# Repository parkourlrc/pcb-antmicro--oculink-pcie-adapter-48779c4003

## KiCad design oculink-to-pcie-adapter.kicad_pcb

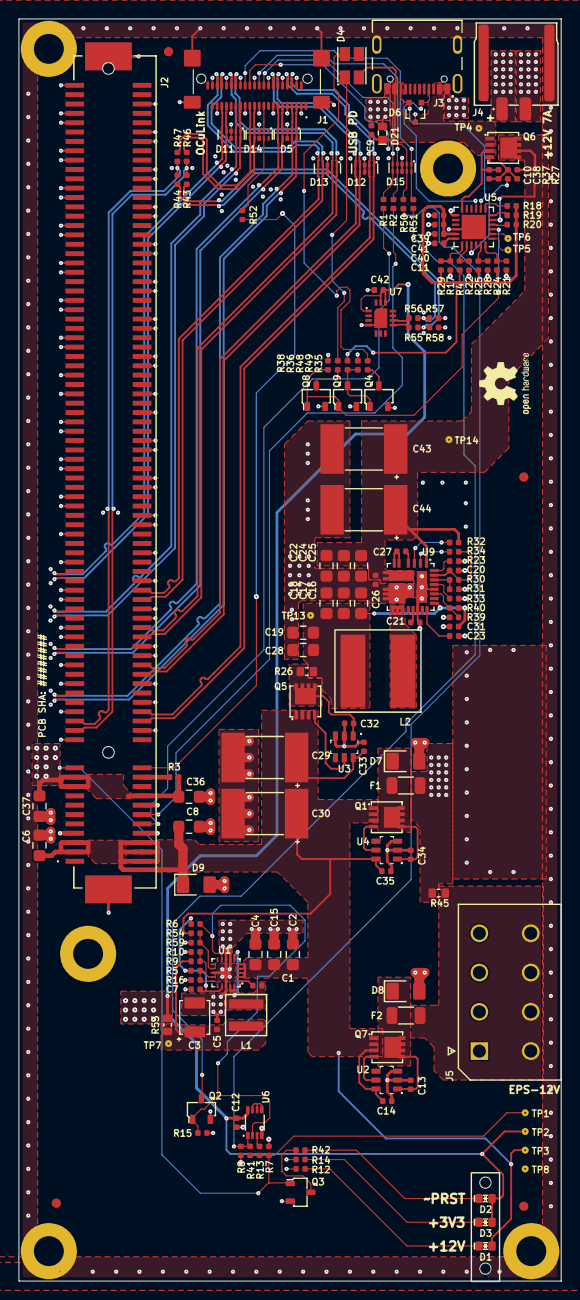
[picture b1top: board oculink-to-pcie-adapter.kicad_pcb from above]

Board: 4 copper layers, 58.0 x 135.0 mm, 159 parts (0 on the bottom side), 97 nets.

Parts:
C1, C12, C13, C26, C27, C31, C32, C34, C40, C41, C42: C_100n_0402; C_0402_1005Metric
C2, C4, C15, C16, C17, C18, C19, C28: C_22u_25V_0805; C_0805_2012Metric
C3: C_Pol_100u_10V_KEMET-T520-B; C_Pol_EIA-B
C5, C7, C10, C11, C14, C20, C33, C35, C38, C39: C_1u_25V_0402; C_0402_1005Metric
C6, C8, C22, C24, C25, C36, C37: C_10u_0805_35V; C_0805_2012Metric
C9, C21: C_4u7_25V_0402; C_0402_1005Metric
C23: C_33n_0402; C_0402_1005Metric
C29, C30, C43, C44: C_Pol_150u_30V_Vishay-T59-EE; C_Pol_Vishay-T59-EE
D1, D2, D3: LED_G_0603_LTST-C190GKT; LED_0603_1608Metric_G
D4: LED_RGB_PLCC4_ASMB_MTB1_0A3A2; PLCC4_3.2x2.8mm
D5, D11, D12, D13, D14, D15: ESD204DQAR; USON-10_2.5x1mm_P0.5mm
D6: TPD2E2U06_SC70; SC70-3
D7, D8, D9: SZSMF4L14AT3G; SOD-123FL
D21: ESDA25P35-1U1M; QFN-2L_1.6x1x0.55mm
F1, F2: F_7A_1206; F_1206_3216Metric
H1: Lightpipe_Mentor_1296.2013; Mech_Lightpipe_Mentor_1296.2013
J1: OCuLink_x4_Amphenol_G14A421211112HR_CUSTOM_device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; Amphenol_G14A421211112HR
J2: PCIe_x16_10146070-113Y0LF-vertical; AMPHENOL_10146070-113Y0LF
J3: USB-C_GCT_USB4105-GF-A; USB-C_Receptacle_GCT_USB4105-GF-A
J4: Molex_Nano-Fit_1x2_SMD_1054301202; Conn_Molex_Nano-Fit_1x2_SMD_1054301202
J5: Molex_Mini-Fit-Jr_2x4_39-28-8080; MOLEX_39288080
L1: L_1u8_6.8A_WE-MAPI-4020; L_WE-MAPI-4020
L2: L_4u7_14.6A_Abracon-Q8080; L_Abracon_ASPIAIG-Q8080
MP1, MP2, MP3, MP4, MP5: MP_Pad6mm_Drill3.2mm
Q1, Q5, Q6, Q7: SQS401EN-T1_BE3; Vishay_PowerPAK_1212-8_Single
Q2, Q3, Q4, Q8, Q9: BSS138-7-F; SOT-23-3
R1, R2, R3, R13, R30, R41, R43, R44, R46, R47, R50, R51, R52: R_0R_0402; R_0402_1005Metric
R4, R14, R17, R21, R22, R24, R25, R28, R29, R37, R42, R48: R_1k_0402; R_0402_1005Metric
R5, R9, R31, R35: R_68k_0402; R_0402_1005Metric
R6, R12, R16, R27, R36, R38, R49, R54: R_10k_0402; R_0402_1005Metric
R7, R8, R15, R32, R34: R_100k_0402; R_0402_1005Metric
R10: R_15k_0402; R_0402_1005Metric
R18, R19, R23: R_2k_0402; R_0402_1005Metric
R20: R_49k9_0402; R_0402_1005Metric
R26, R45, R53: R_0R_22.4A_0603; R_0603_1608Metric
R33: R_158k_0402; R_0402_1005Metric
R39: R_10k_0.1%_0402; R_0402_1005Metric
R40: R_140k_0.1%_0402; R_0402_1005Metric
R55, R56: R_22R_0402; R_0402_1005Metric
R57, R58: R_50R_0402; R_0402_1005Metric
R59: R_1k5_0402; R_0402_1005Metric
TP1, TP2, TP3, TP4, TP5, TP6, TP7, TP8, TP13, TP14: TP_Pad0.75mm_Drill0.2mm
U1: TPS56C230; QFN-20-1EP_3x3mm_P0.45mm
U2, U3, U4: LTC4412IS6; SOT-23-6
U5: CYPD3177-24LQXQ; QFN-24-1EP_4x4mm_P0.5mm_EP2.6x2.6mm
U6: 74AUP2G132; VSSOP-8_2.3x2mm_P0.5mm
U7: DSC557-0343FI1; VQFN-14-1EP_3.2x2.5mm_P0.5mm_Layout4x3
U9: SIC477ED-T1-GE3; SIC47XED-T1-GE3

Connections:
+3V3: C12.2, C36.1, C37.1, C42.2, D2.2 (A), D3.2 (A), J2.A9, J2.A10, J2.B8, R3.1, R53.1, TP2.1, U6.8 (VCC), U7.1 (OE), U7.12 (VDD1), U7.13 (VDD0)
+12V: C2.2, C4.2, C6.1, C8.1, C14.2, C15.2, C29.1, C30.1, C33.2, C35.2, D1.2 (A), D9.1 (C), J2.A2, J2.A3, J2.B1, J2.B2, J2.B3, Q1.1 (S), Q1.2 (S), Q1.3 (S), Q5.1 (S), Q5.2 (S), Q5.3 (S), Q7.1 (S), Q7.2 (S), Q7.3 (S), R54.1, TP3.1, U1.2 (V_{IN}), U1.3 (V_{IN}), U1.4 (V_{IN}), U1.5 (V_{IN}), U2.6 (SENSE), U3.6 (SENSE), U4.6 (SENSE)
/OCuLink/I2C0.SCL: J2.B5, R1.2
/OCuLink/I2C0.SDA: J2.B6, R2.2
/OCuLink/I2C0C_SCL: D15.5, D15.6, J1.A9 (SCL), R1.1
/OCuLink/I2C0C_SDA: D15.4, D15.7, J1.A10 (SDA), R2.1
/OCuLink/PCIe_{REF0}.CK+: J2.A13, R43.2, R46.2
/OCuLink/PCIe_{REF0}.CK-: J2.A14, R44.2, R47.2
/OCuLink/PCIe_{REF0}_R.CK+: D14.4, D14.7, J1.B12 (VSP1), R46.1
/OCuLink/PCIe_{REF0}_R.CK-: D14.5, D14.6, J1.B13 (VSP2), R47.1
/OCuLink/PCIe_{x4}.RX0+: D5.1, D5.10, J1.B3 (PET0+), J2.A16
/OCuLink/PCIe_{x4}.RX0-: D5.2, D5.9, J1.B4 (PET0-), J2.A17
/OCuLink/PCIe_{x4}.RX1+: D5.4, D5.7, J1.B6 (PET1+), J2.A21
/OCuLink/PCIe_{x4}.RX1-: D5.5, D5.6, J1.B7 (PET1-), J2.A22
/OCuLink/PCIe_{x4}.RX2+: D11.1, D11.10, J1.B15 (PET2+), J2.A25
/OCuLink/PCIe_{x4}.RX2-: D11.2, D11.9, J1.B16 (PET2-), J2.A26
/OCuLink/PCIe_{x4}.RX3+: D11.4, D11.7, J1.B18 (PET3+), J2.A29
/OCuLink/PCIe_{x4}.RX3-: D11.5, D11.6, J1.B19 (PET3-), J2.A30
/OCuLink/PCIe_{x4}.TX0+: D12.1, D12.10, J1.A3 (PER0+), J2.B14
/OCuLink/PCIe_{x4}.TX0-: D12.2, D12.9, J1.A4 (PER0-), J2.B15
/OCuLink/PCIe_{x4}.TX1+: D12.4, D12.7, J1.A6 (PER1+), J2.B19
/OCuLink/PCIe_{x4}.TX1-: D12.5, D12.6, J1.A7 (PER1-), J2.B20
/OCuLink/PCIe_{x4}.TX2+: D13.1, D13.10, J1.A15 (PER2+), J2.B23
/OCuLink/PCIe_{x4}.TX2-: D13.2, D13.9, J1.A16 (PER2-), J2.B24
/OCuLink/PCIe_{x4}.TX3+: D13.4, D13.7, J1.A18 (PER3+), J2.B27
/OCuLink/PCIe_{x4}.TX3-: D13.5, D13.6, J1.A19 (PER3-), J2.B28
/OCuLink/~CPRSNTC: D15.1, D15.10, J1.A13 (~CPRSNT), R51.1
/OCuLink/~CPRSNT: Q2.3 (D), R51.2
/OCuLink/~PERSTC: D15.2, D15.9, J1.A12 (~PERST), R50.1
/OCuLink/~WAKEC: D14.2, D14.9, J1.B10 (~CWAKE), R52.1
/OCuLink/~WAKE: J2.B11, R52.2
/PCIe-clock-generator/PCIe_{REF1}_R2.CK+: R55.1, U7.8 (CLK1+)
/PCIe-clock-generator/PCIe_{REF1}_R2.CK-: R56.1, U7.9 (CLK1-)
/PCIe-clock-generator/PCIe_{REF1}_R.CK+: R43.1, R55.2, R58.2
/PCIe-clock-generator/PCIe_{REF1}_R.CK-: R44.1, R56.2, R57.2
/PCIe-connector/3V3_PCIe_AUX: J2.B10, R3.2
/Power/3V3_BST: C1.1, U1.1 (BST)
/Power/3V3_CONV: C3.1, C5.2, L1.2, R9.2, R53.2, TP7.1
/Power/3V3_EN: R54.2, R59.2, U1.12 (EN)
/Power/3V3_FB: R9.1, R10.2, U1.14 (FB)
/Power/3V3_MODE: R5.1, R16.1, U1.15 (MODE)
/Power/3V3_PG: Q2.1 (G), R6.2, R15.2, U1.9 (PG), U6.2 (1B)
/Power/3V3_SW: C1.2, L1.1, U1.6 (SW), U1.19 (SW), U1.20 (SW)
/Power/3V3_VCC: C7.2, R5.2, R6.1, U1.17 (V_{CC})
/Power/Ideal-diode-1/VIN: C34.2, D7.1 (C), F1.2, Q1.5 (D), U4.1 (IN)
/Power/Ideal-diode-2/VIN: C13.2, D8.1 (C), F2.2, Q7.5 (D), U2.1 (IN)
/Power/PERST: U6.5 (2A), U6.6 (2B), U6.7 (1Y)
/Power/VCC_DC_CONN_1: F1.1, J4.1, R45.2
/Power/VCC_DC_CONN_2: F2.1, J5.5, J5.6, J5.7, J5.8, R45.1
/Power/VCC_PD: C32.2, Q5.5 (D), R26.1, U3.1 (IN)
/Power/~PERST_CONN: R8.2, R41.1, R50.2, U6.1 (1A)
/Power/~PERST: J2.A11, Q3.1 (G), R7.2, R13.2, R41.2, TP1.1
/USB-PD/12V_BOOT: C27.1, U9.4 (BOOT)
/USB-PD/12V_CONV: C16.2, C17.2, C18.2, C19.2, C28.2, C31.2, L2.2, R26.2, R40.2, TP13.1, U9.20 (V_{SNS})
/USB-PD/12V_EN: R32.1, U9.3 (EN)
/USB-PD/12V_FB: R39.2, R40.1, U9.22 (V_{FB})
/USB-PD/12V_FSW: R33.2, U9.24 (f_{SW})
/USB-PD/12V_ILIM: R30.2, R31.2, U9.25 (I_{LIMIT})
/USB-PD/12V_MODE: R23.1, U9.27 (MODE)
/USB-PD/12V_PG: R34.1, U9.2 (P_{GOOD})
/USB-PD/12V_SS: C23.1, U9.19 (SS)
/USB-PD/12V_SW: L2.1, U9.12 (SW), U9.13 (SW), U9.14 (SW)
/USB-PD/12V_VDD: C20.2, R30.1, R34.2, U9.26 (V_{DD})
/USB-PD/12V_VDRV: C21.2, U9.16 (V_{DRV})
/USB-PD/CC1: D6.1, J3.A5 (CC_{1}), U5.15 (CC1)
/USB-PD/CC2: D6.2, J3.B5 (CC_{2}), U5.14 (CC2)
/USB-PD/FAULT: Q8.1 (G), Q9.1 (G), R38.2, U5.9 (FAULT)
/USB-PD/FLIP: R20.1, U5.10 (FLIP)
/USB-PD/GPIO_1: TP6.1, U5.8 (GPIO_1)
/USB-PD/ISNK_COARSE: R25.1, R28.2, U5.5 (ISNK_COARSE)
/USB-PD/ISNK_FINE: R21.2, R24.1, U5.6 (ISNK_FINE)
/USB-PD/SCL: R18.1, U5.13 (HPI_SCL)
/USB-PD/SDA: R19.1, U5.12 (HPI_SDA)
/USB-PD/VBUS_EN: R37.1, U5.3 (VBUS_FET_EN)
/USB-PD/VBUS_MAX: R4.1, R22.2, U5.2 (VBUS_MAX)
/USB-PD/VBUS_MIN: R17.2, R29.1, U5.1 (VBUS_MIN)
/USB-PD/VCC: C22.2, C24.2, C25.2, C26.2, C38.2, C43.1, C44.1, Q6.5 (D), R32.2, TP14.1, U5.11 (VDC_OUT), U9.1 (V_{CIN}), U9.7 (V_{IN}), U9.8 (V_{IN})
/USB-PD/VCCD_1V8: C11.2, U5.24 (VCCD)
/USB-PD/VDDD_3V3: C39.2, C40.2, C41.2, R4.2, R18.2, R19.2, R20.2, R24.2, R25.2, R29.2, R48.2, U5.23 (VDDD)
/USB-PD/~FAULT: Q4.1 (G), Q9.3 (D), R48.1, R49.2
/USB-PD/~HPI_INT: TP5.1, U5.7 (~HPI_INT)
GND: C2.1, C3.2, C4.1, C5.1, C6.2, C7.1, C8.2, C9.1, C11.1, C12.1, C13.1, C14.1, C15.1, C16.1, C17.1, C18.1, C19.1, C20.1, C21.1, C22.1, C23.2, C24.1, C25.1, C26.1, C28.1, C29.2, C30.2, C31.1, C32.1, C33.1, C34.1, C35.1, C36.2, C37.2, C39.1, C40.1, C41.1, C42.1, C43.2, C44.2, D5.3, D5.8, D6.3, D7.2 (A), D8.2 (A), D9.2 (A), D11.3, D11.8, D12.3, D12.8, D13.3, D13.8, D14.3, D14.8, D15.3, D15.8, D21.2 (A), J1.A2 (GND), J1.A5 (GND), J1.A8 (GND), J1.A11 (GND), J1.A14 (GND), J1.A17 (GND), J1.A20 (GND), J1.B2 (GND), J1.B5 (GND), J1.B8 (GND), J1.B11 (GND), J1.B14 (GND), J1.B17 (GND), J1.B20 (GND), J1.SH, J2.A4, J2.A12, J2.A15, J2.A18, J2.A20, J2.A23, J2.A24, J2.A27, J2.A28, J2.A31, J2.A34, J2.A37, J2.A38, J2.A41, J2.A42, J2.A45, J2.A46, J2.A49, J2.A51, J2.A54, J2.A55, J2.A58, J2.A59, J2.A62, J2.A63, J2.A66, J2.A67, J2.A70, J2.A71, J2.A74, J2.A75, J2.A78, J2.A79, J2.A82, J2.B4, J2.B7, J2.B13, J2.B16, J2.B18, J2.B21, J2.B22, J2.B25, J2.B26, J2.B29, J2.B32, J2.B35, J2.B36, J2.B39, J2.B40, J2.B43, J2.B44, J2.B47, J2.B49, J2.B52, J2.B53, J2.B56, J2.B57, J2.B60, J2.B61, J2.B64, J2.B65, J2.B68, J2.B69, J2.B72, J2.B73, J2.B76, J2.B77, J2.B80, J2.S1, J2.S2, J3.A1 (GND), J3.A12 (GND), J3.B1 (GND), J3.B12 (GND), J3.SH, J4.2, J4.MP, J5.1, J5.2, J5.3, J5.4, MP1.1, MP2.1, MP3.1, MP4.1, MP5.1, Q2.2 (S), Q3.2 (S), Q4.2 (S), Q8.2 (S), Q9.2 (S), R7.1, R8.1, R10.1, R12.1, R14.1, R15.1, R16.2, R17.1, R21.1, R22.1, R23.2, R28.1, R31.1, R33.1, R38.1, R39.1, R49.1, R57.1, R58.1, R59.1, TP8.1, U1.7 (PGND), U1.8 (PGND), U1.13 (AGND), U1.18 (PGND), U1.21 (PGND), U2.2 (GND), U2.3 (CTL), U3.2 (GND), U3.3 (CTL), U4.2 (GND), U4.3 (CTL), U5.19 (GND), U5.22 (GND), U5.25 (GND), U6.4 (GND), U7.4 (VSS), U7.15 (EPAD), U9.9 (PGND), U9.10 (PGND), U9.11 (PGND), U9.17 (PGND), U9.23 (AGND), U9.28 (AGND)
unnamed: C27.2, U9.5 (PHASE), U9.6 (PHASE)
unnamed: D1.1 (C), R12.2
unnamed: D2.1 (C), R42.2
unnamed: D3.1 (C), R14.2
unnamed: D4.2 (C_{G}), R35.2
unnamed: D4.1 (C_{R}), R36.2
unnamed: Q1.4 (G), U4.5 (GATE)
unnamed: Q3.3 (D), R42.1
unnamed: Q4.3 (D), R35.1
unnamed: Q5.4 (G), U3.5 (GATE)
unnamed: C10.1, C38.1, Q6.4 (G), R27.1, R37.2
unnamed: Q7.4 (G), U2.5 (GATE)
unnamed: Q8.3 (D), R36.1
unnamed: R13.1, U6.3 (2Y)
VBUS: C9.2, C10.2, D4.4 (A), D21.1 (C), J3.A4 (VBUS), J3.A9 (VBUS), J3.B4 (VBUS), J3.B9 (VBUS), Q6.1 (S), Q6.2 (S), Q6.3 (S), R27.2, TP4.1, U5.18 (VBUS_IN)

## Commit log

2025-07-22 [#80490] Fixed missing solder mask opening on J2
2025-09-09 [#80490] Updated J2 footprint

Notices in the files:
parts and their libraries:
License: Apache-2.0
